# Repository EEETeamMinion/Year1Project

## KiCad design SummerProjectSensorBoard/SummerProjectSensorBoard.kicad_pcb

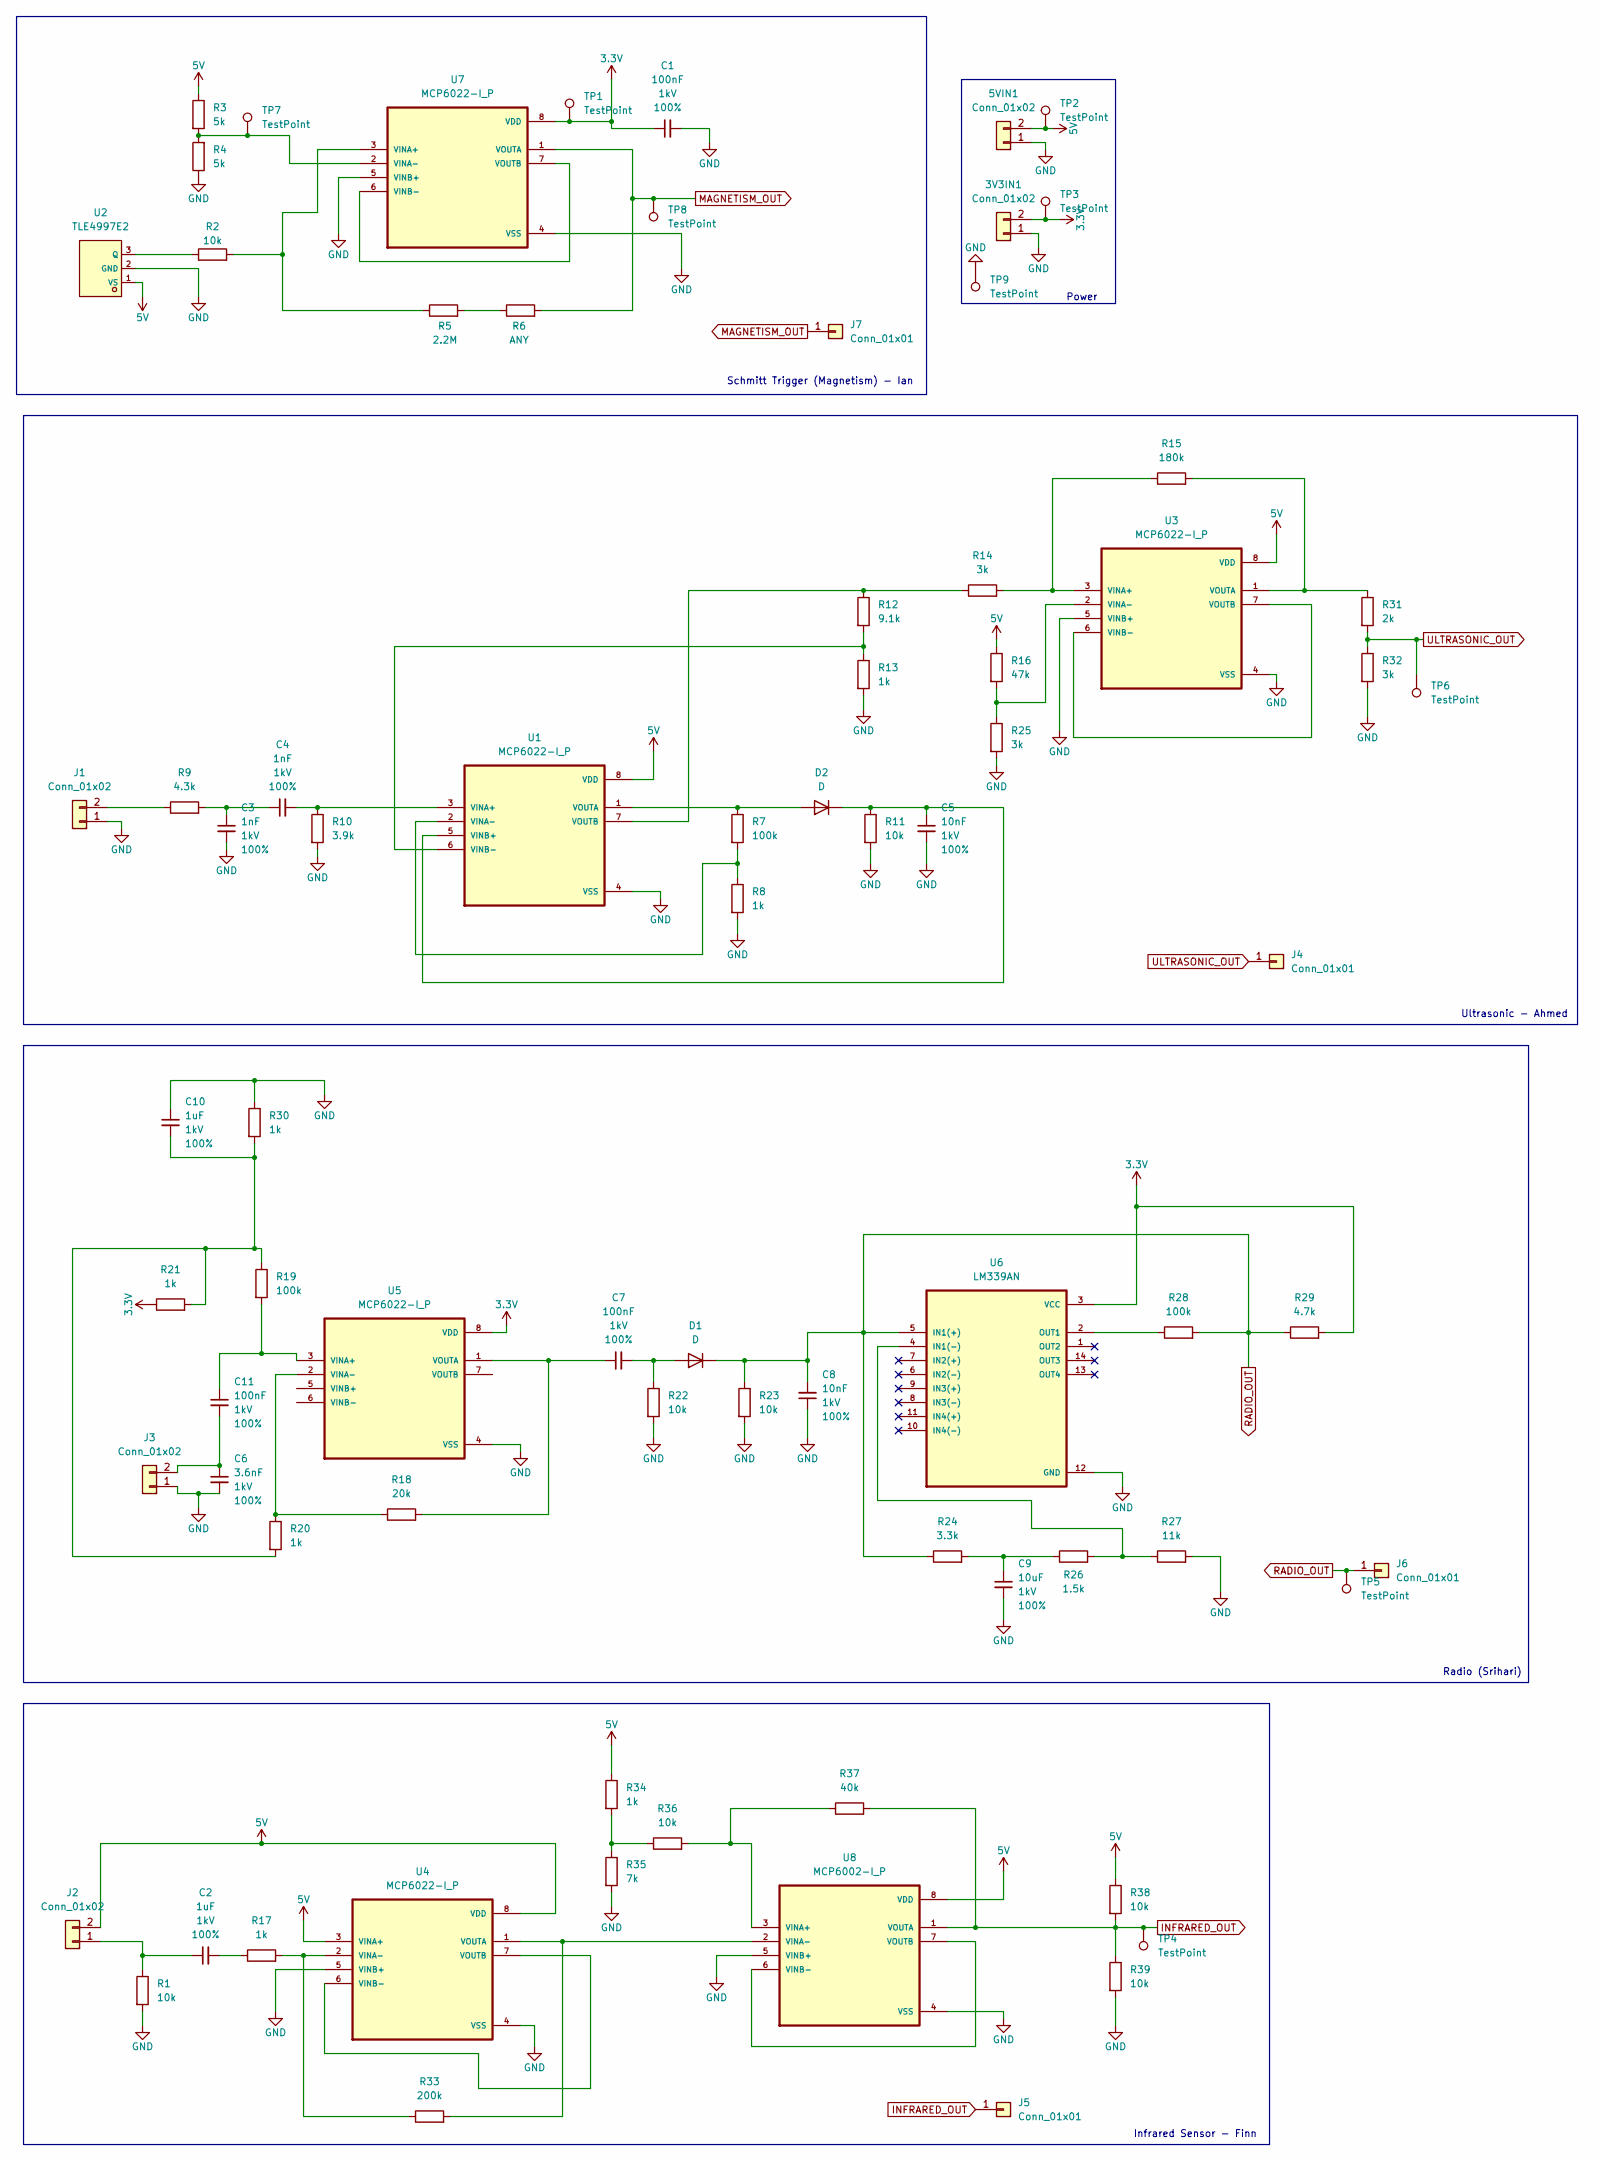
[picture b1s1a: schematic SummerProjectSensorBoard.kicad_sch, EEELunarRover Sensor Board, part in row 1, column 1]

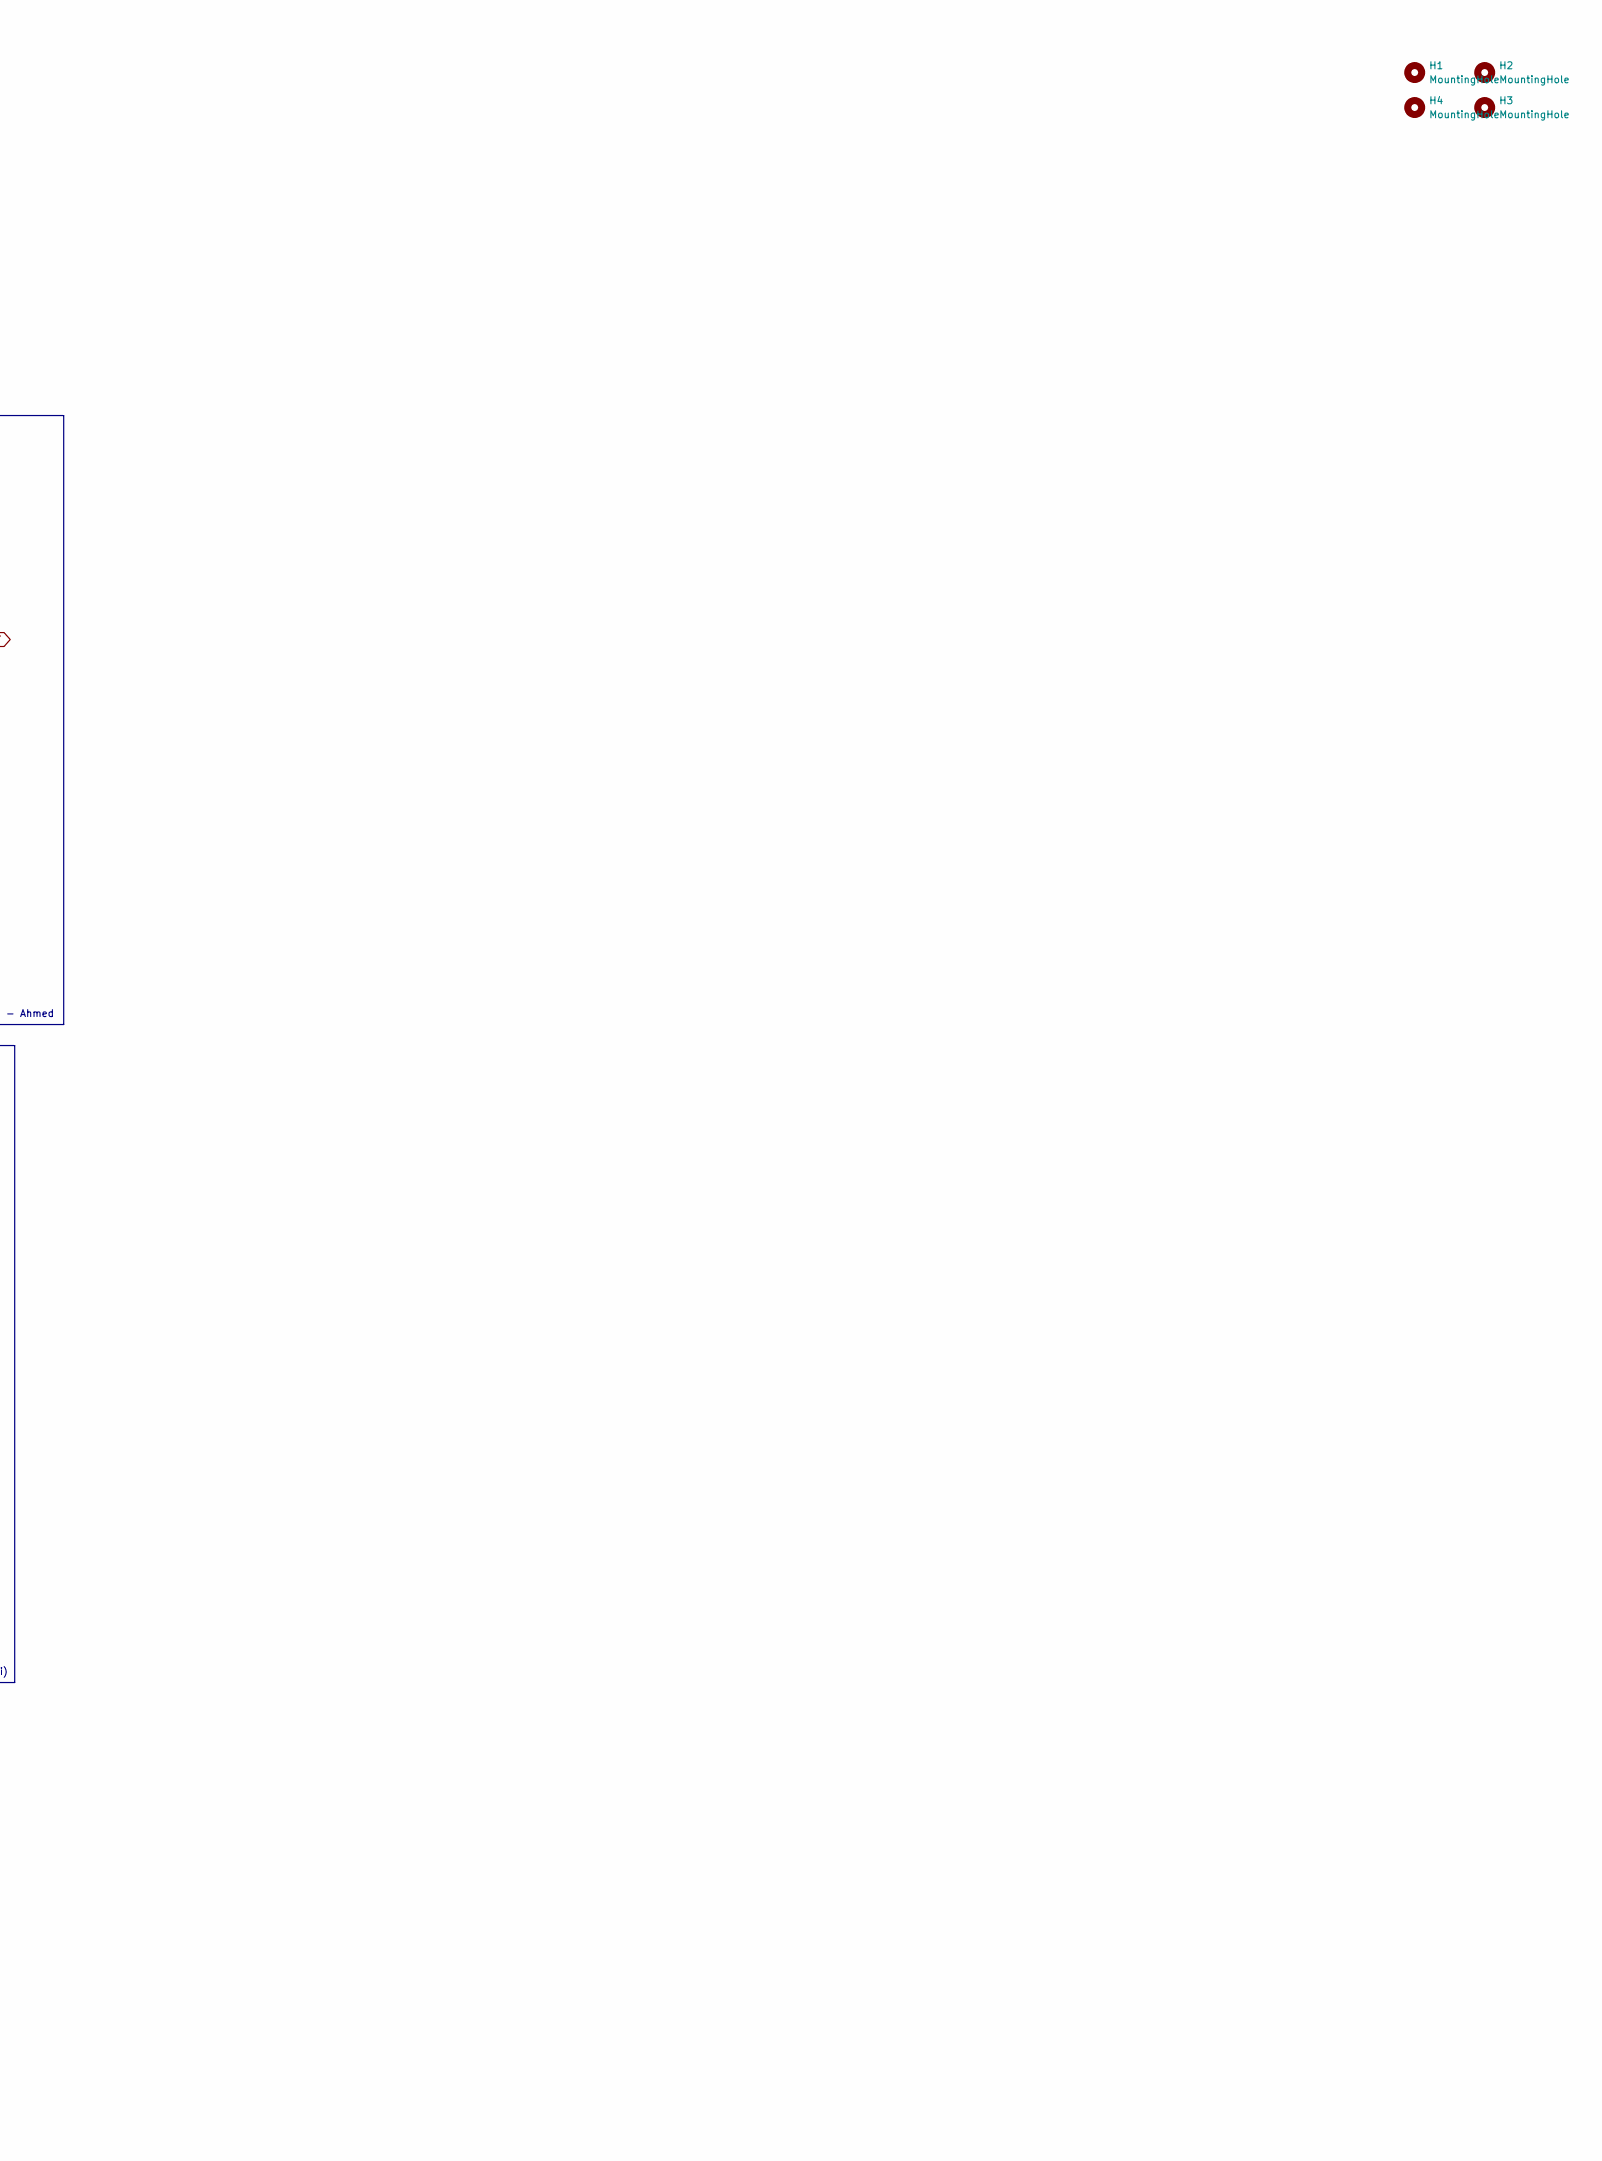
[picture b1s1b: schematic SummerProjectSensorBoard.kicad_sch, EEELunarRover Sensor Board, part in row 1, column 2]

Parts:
3V3IN1, 5VIN1: Conn_01x02; JST_EH_B2B-EH-A_1x02_P2.50mm_Vertical
C1, C7, C11: 100nF; C_Disc_D5.0mm_W2.5mm_P2.50mm; Voltage 1kV; Tolerance 100%
C2: 1uF; C_Disc_D5.0mm_W2.5mm_P2.50mm; Voltage 1kV; Tolerance 100%
C3, C4: 1nF; C_Disc_D5.0mm_W2.5mm_P2.50mm; Voltage 1kV; Tolerance 100%
C5, C8: 10nF; C_Disc_D5.0mm_W2.5mm_P2.50mm; Voltage 1kV; Tolerance 100%
C6: 3.6nF; C_Disc_D5.0mm_W2.5mm_P5.00mm; Voltage 1kV; Tolerance 100%
C9: 10uF; C_Radial_D6.3mm_H5.0mm_P2.50mm; Voltage 1kV; Tolerance 100%
C10: 1uF; C_Radial_D6.3mm_H5.0mm_P2.50mm; Voltage 1kV; Tolerance 100%
D1, D2: D; D_5W_P10.16mm_Horizontal
H1, H2, H3, H4: MountingHole; MountingHole_3.2mm_M3
J1, J2, J3: Conn_01x02; JST_PH_B2B-PH-K_1x02_P2.00mm_Vertical
J4, J5, J6, J7: Conn_01x01; PinHeader_1x01_P1.00mm_Vertical
R1, R2, R11, R22, R23, R36, R38, R39: 10k; R_Axial_DIN0207_L6.3mm_D2.5mm_P7.62mm_Horizontal
R3, R4: 5k; R_Axial_DIN0207_L6.3mm_D2.5mm_P7.62mm_Horizontal
R5: 2.2M; R_Axial_DIN0207_L6.3mm_D2.5mm_P7.62mm_Horizontal
R6: ANY; R_Axial_DIN0207_L6.3mm_D2.5mm_P7.62mm_Horizontal
R7, R19, R28: 100k; R_Axial_DIN0207_L6.3mm_D2.5mm_P7.62mm_Horizontal
R8, R13, R17, R20, R21, R30, R34: 1k; R_Axial_DIN0207_L6.3mm_D2.5mm_P7.62mm_Horizontal
R9: 4.3k; R_Axial_DIN0207_L6.3mm_D2.5mm_P7.62mm_Horizontal
R10: 3.9k; R_Axial_DIN0207_L6.3mm_D2.5mm_P7.62mm_Horizontal
R12: 9.1k; R_Axial_DIN0207_L6.3mm_D2.5mm_P7.62mm_Horizontal
R14, R25, R32: 3k; R_Axial_DIN0207_L6.3mm_D2.5mm_P7.62mm_Horizontal
R15: 180k; R_Axial_DIN0207_L6.3mm_D2.5mm_P7.62mm_Horizontal
R16: 47k; R_Axial_DIN0207_L6.3mm_D2.5mm_P7.62mm_Horizontal
R18: 20k; R_Axial_DIN0207_L6.3mm_D2.5mm_P7.62mm_Horizontal
R24: 3.3k; R_Axial_DIN0207_L6.3mm_D2.5mm_P7.62mm_Horizontal
R26: 1.5k; R_Axial_DIN0207_L6.3mm_D2.5mm_P7.62mm_Horizontal
R27: 11k; R_Axial_DIN0207_L6.3mm_D2.5mm_P7.62mm_Horizontal
R29: 4.7k; R_Axial_DIN0207_L6.3mm_D2.5mm_P7.62mm_Horizontal
R31: 2k; R_Axial_DIN0207_L6.3mm_D2.5mm_P7.62mm_Horizontal
R33: 200k; R_Axial_DIN0207_L6.3mm_D2.5mm_P7.62mm_Horizontal
R35: 7k; R_Axial_DIN0207_L6.3mm_D2.5mm_P7.62mm_Horizontal
R37: 40k; R_Axial_DIN0207_L6.3mm_D2.5mm_P7.62mm_Horizontal
TP1, TP2, TP3, TP4, TP5, TP6, TP7, TP8, TP9: TestPoint; TestPoint_Pad_D1.5mm
U1, U3, U4, U5, U7: MCP6022-I_P; DIP787W46P254L927H533Q8
U2: TLE4997E2; C539897_PG-SSO-3-2_L4_2-W1_5-P1_27-L; LCSC C539897
U6: LM339AN; DIP794W45P254L1969H508Q14
U8: MCP6002-I_P; DIP787W46P254L927H533Q8

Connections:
3.3V: 3V3IN1.2, C1.1, R21.1, R29.2, TP1.1, TP3.1, U5.8 (VDD), U6.3 (VCC), U7.8 (VDD)
5V: 5VIN1.2, J2.2, R3.1, R16.1, R34.1, R38.1, TP2.1, U1.8 (VDD), U2.1 (VS), U3.8 (VDD), U4.3 (VINA+), U4.8 (VDD), U8.8 (VDD)
GND: 3V3IN1.1, 5VIN1.1, C1.2, C3.2, C5.2, C6.2, C8.1, C9.2, C10.1, J1.1, J3.1, R1.2, R4.1, R8.2, R10.2, R11.2, R13.2, R22.2, R23.2, R25.2, R27.2, R30.1, R32.2, R35.2, R39.2, TP9.1, U1.4 (VSS), U2.2 (GND), U3.4 (VSS), U3.5 (VINB+), U4.4 (VSS), U4.5 (VINB+), U5.4 (VSS), U6.12 (GND), U7.4 (VSS), U7.5 (VINB+), U8.4 (VSS), U8.5 (VINB+)
INFRARED_OUT: J5.1, R37.2, R38.2, R39.1, TP4.1, U8.1 (VOUTA)
MAGNETISM_OUT: J7.1, R6.2, TP8.1, U7.1 (VOUTA)
unnamed: C2.2, R17.1
unnamed: C3.1, C4.1, R9.2
unnamed: C9.1, R24.2, R26.1
unnamed: C10.2, R19.1, R20.2, R21.2, R30.2
unnamed: C7.2, D1.2 (A), R22.1
unnamed: D2.2 (A), R7.1, U1.1 (VOUTA)
unnamed: C5.1, D2.1 (K), R11.1, U1.5 (VINB+)
unnamed: J1.2, R9.1
unnamed: C2.1, J2.1, R1.1
unnamed: C6.1, C11.2, J3.2
unnamed: R5.2, R6.1
unnamed: R34.2, R35.1, R36.1
unnamed: C4.2, R10.1, U1.3 (VINA+)
unnamed: R7.2, R8.1, U1.2 (VINA-)
unnamed: R12.2, R13.1, U1.6 (VINB-)
unnamed: R12.1, R14.1, U1.7 (VOUTB)
unnamed: R2.1, U2.3 (Q)
unnamed: R14.2, R15.1, U3.3 (VINA+)
unnamed: R16.2, R25.1, U3.2 (VINA-)
unnamed: U3.6 (VINB-), U3.7 (VOUTB)
unnamed: R15.2, R31.1, U3.1 (VOUTA)
unnamed: R17.2, R33.1, U4.2 (VINA-)
unnamed: U4.6 (VINB-), U4.7 (VOUTB)
unnamed: R33.2, U4.1 (VOUTA), U8.2 (VINA-)
unnamed: C11.1, R19.2, U5.3 (VINA+)
unnamed: R18.1, R20.1, U5.2 (VINA-)
unnamed: C7.1, R18.2, U5.1 (VOUTA)
unnamed: R26.2, R27.1, U6.4 (IN1(-))
unnamed: R28.1, U6.2 (OUT1)
unnamed: R2.2, R5.1, U7.3 (VINA+)
unnamed: R3.2, R4.2, TP7.1, U7.2 (VINA-)
unnamed: U7.6 (VINB-), U7.7 (VOUTB)
unnamed: R36.2, R37.1, U8.3 (VINA+)
unnamed: U8.6 (VINB-), U8.7 (VOUTB)
RADIO_OUT: C8.2, D1.1 (K), J6.1, R23.1, R24.1, R28.2, R29.1, TP5.1, U6.5 (IN1(+))
ULTRASONIC_OUT: J4.1, R31.2, R32.1, TP6.1

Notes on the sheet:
Radio (Srihari)
Power
Infrared Sensor - Finn
Ultrasonic - Ahmed
Schmitt Trigger (Magnetism) - Ian

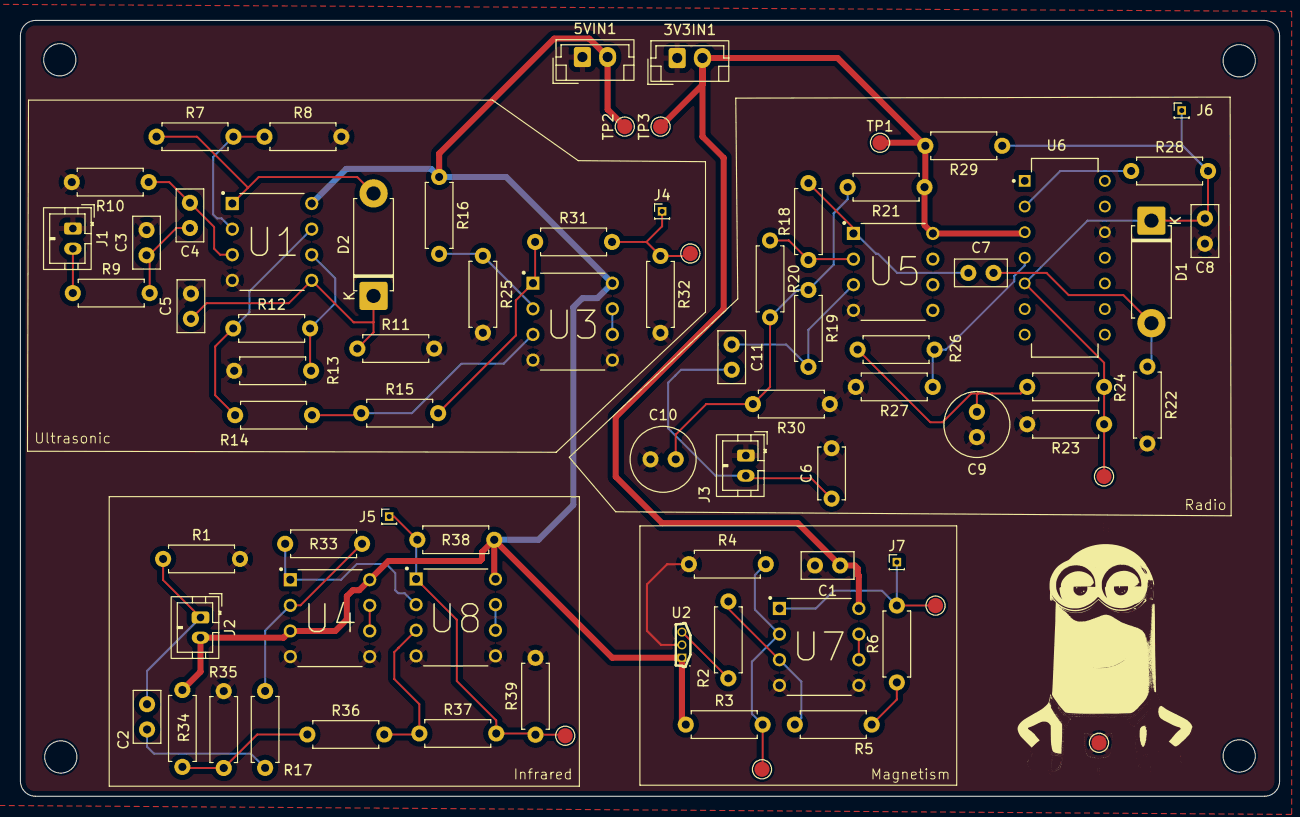
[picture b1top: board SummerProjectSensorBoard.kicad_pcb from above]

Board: 2 copper layers, 124.8 x 76.9 mm, 82 parts (0 on the bottom side), 41 nets.

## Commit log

2026-05-13 Add files via upload
    Here is the breakdown of the antennae being built
2026-05-13 Update Building the Antennae.md
    Editing latex
2026-06-10 Create Magnetism
2026-06-10 Create test
2026-06-16 Rename Building the Antennae.md to Radio/Building the Antennae.md
